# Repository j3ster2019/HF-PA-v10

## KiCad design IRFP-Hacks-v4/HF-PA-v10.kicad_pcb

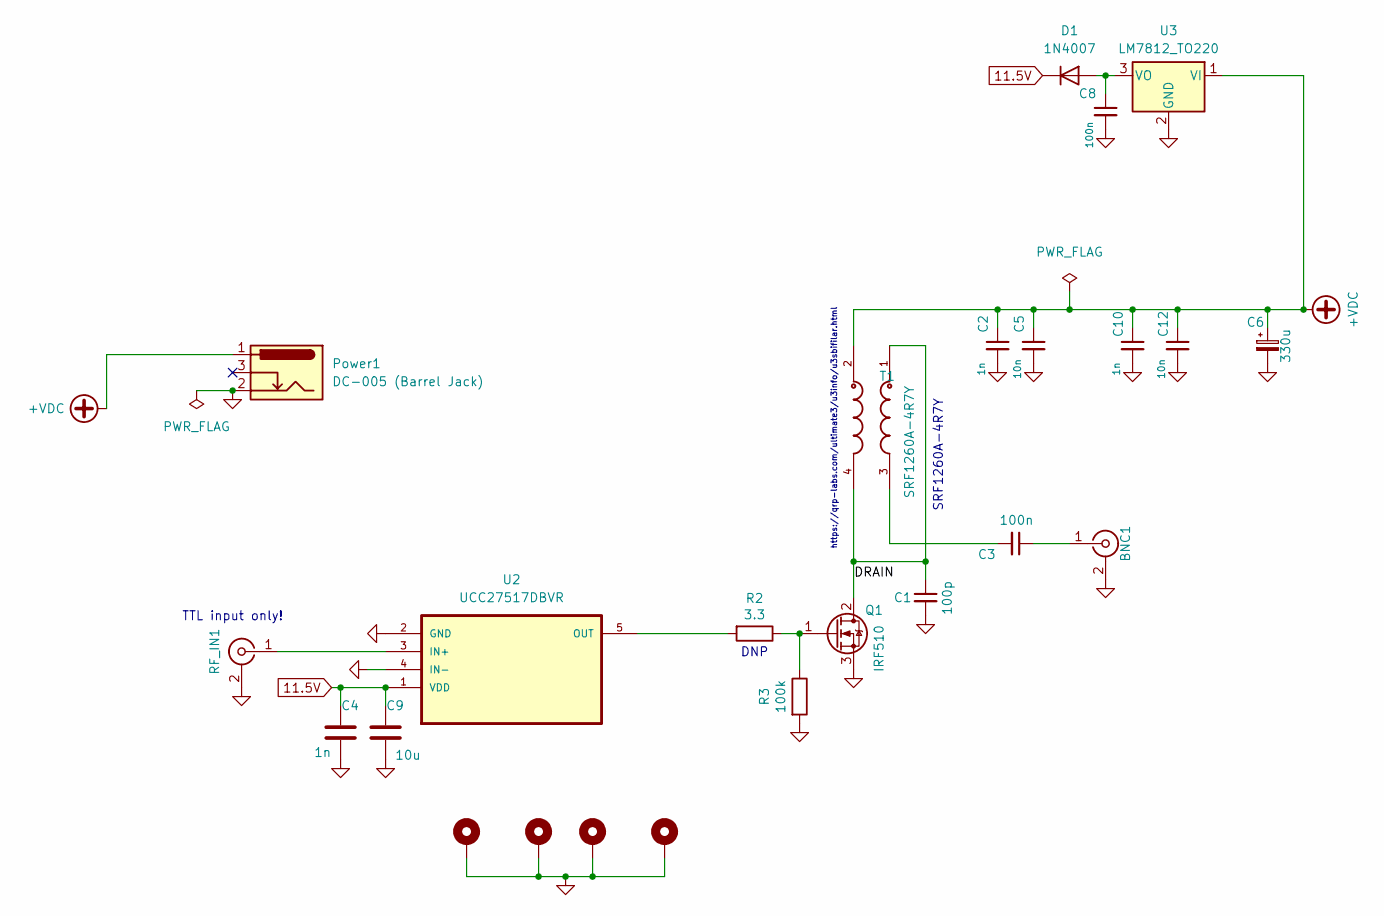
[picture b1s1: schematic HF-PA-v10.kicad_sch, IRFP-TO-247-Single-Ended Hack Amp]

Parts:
BNC1: SMA; SMA_Samtec_SMA-J-P-X-ST-EM1_EdgeMount
C1: 100p; C_1206_3216Metric_Pad1.33x1.80mm_HandSolder
C2, C4, C10: 1n; C_1206_3216Metric_Pad1.33x1.80mm_HandSolder
C3, C8: 100n; C_1206_3216Metric_Pad1.33x1.80mm_HandSolder
C5, C12: 10n; C_1206_3216Metric_Pad1.33x1.80mm_HandSolder
C6: 330u; CP_Radial_D8.0mm_P5.00mm
C9: 10u; C_1206_3216Metric_Pad1.33x1.80mm_HandSolder
D1: 1N4007; D_DO-41_SOD81_P2.54mm_Vertical_KathodeUp
H1, H2, H3, H4: MountingHole_Pad; MountingHole_3.2mm_M3_Pad_Via
Power1: DC-005 (Barrel Jack); XKB_DC-005-5A-2.0_Modded
Q1: IRF510; TO-247-3_Horizontal_TabDown_Modded
R2: 3.3; R_1206_3216Metric_Pad1.30x1.75mm_HandSolder
R3: 100k; R_1206_3216Metric_Pad1.30x1.75mm_HandSolder
RF_IN1: SMA; SMA_Samtec_SMA-J-P-X-ST-EM1_EdgeMount
T1: SRF1260A-4R7Y; IND_SRF1260A-4R7Y-Longer-Pads
U2: UCC27517DBVR; TSOT-23-5_HandSoldering
U3: LM7812_TO220; TO-220-3_Horizontal_TabDown

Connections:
11.5V: C4.1, C9.1, D1.1 (K), U2.1 (VDD)
+VDC: C2.1, C5.1, C6.1, C10.1, C12.1, Power1.1, T1.2, U3.1 (VI)
/DRAIN: C1.1, Q1.2 (D), T1.1, T1.4
GND: C1.2, C2.2, C4.2, C5.2, C6.2, C8.2, C9.2, C10.2, C12.2, H1.1, H2.1, H3.1, H4.1, Power1.2, Q1.3 (S), R3.2, RF_IN1.2 (Ext), U2.2 (GND), U2.4 (IN-), U3.2 (GND); also elsewhere on the board
unnamed: C3.2, T1.3
unnamed: C8.1, D1.2 (A), U3.3 (VO)
unnamed: Q1.1 (G), R2.1, R3.1
unnamed: RF_IN1.1 (In), U2.3 (IN+)
unnamed 8: C3.1; also elsewhere on the board
unnamed: R2.2, U2.5 (OUT)

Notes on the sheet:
DNP
https://qrp-labs.com/ultimate3/u3info/u3sbifilar.html
SRF1260A-4R7Y
TTL input only!

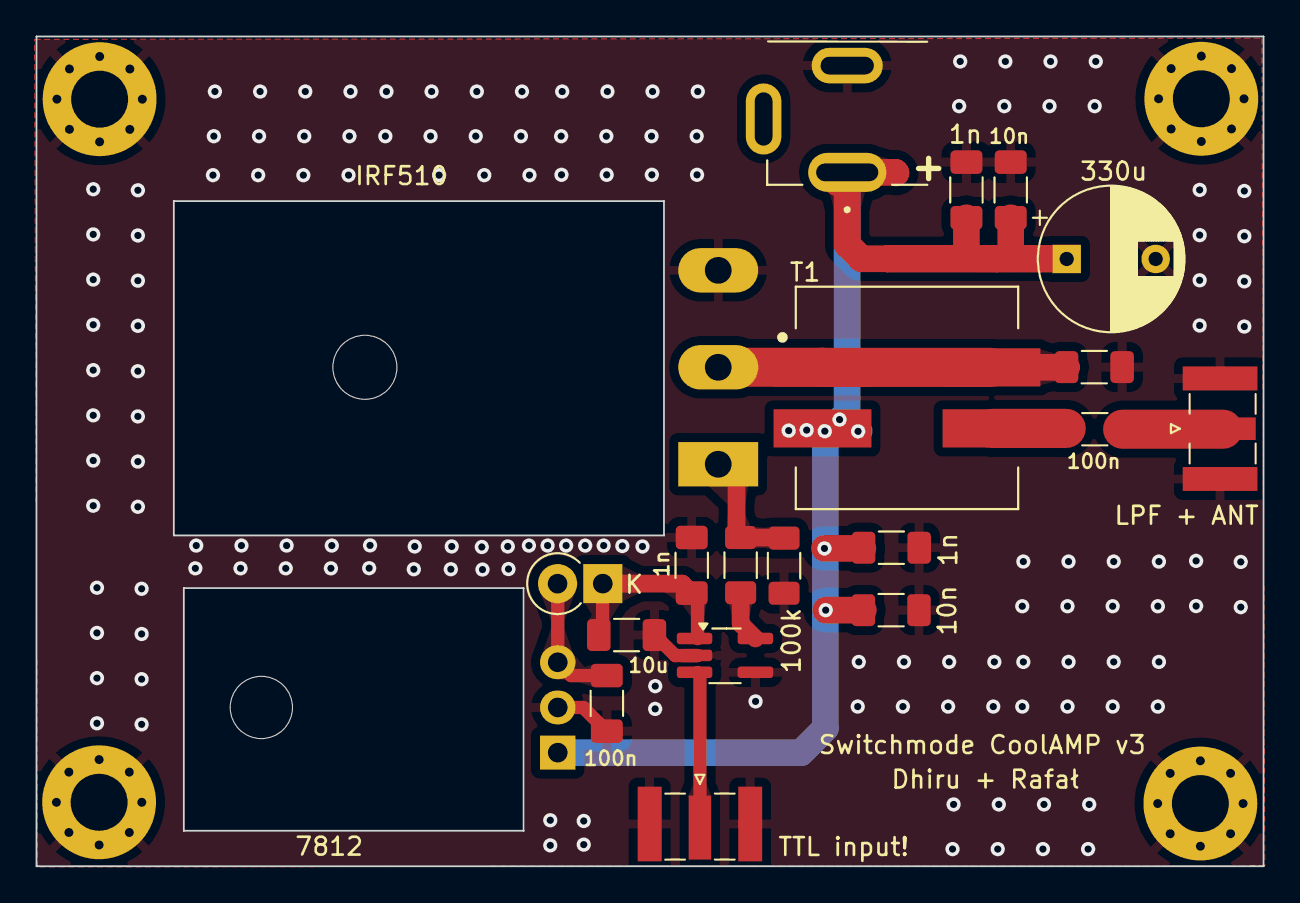
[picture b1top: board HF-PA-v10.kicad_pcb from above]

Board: 2 copper layers, 69.0 x 46.6 mm, 24 parts (0 on the bottom side), 10 nets.

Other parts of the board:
RF_OUT1: SMA; SMA_Samtec_SMA-J-P-X-ST-EM1_EdgeMount

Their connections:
GND: RF_OUT1.2 (Ext); also elsewhere on the board
unnamed 8: RF_OUT1.1 (In); also elsewhere on the board

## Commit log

2024-05-09 Initial version
